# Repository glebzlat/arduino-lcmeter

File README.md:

## Arduino LC-meter

Простой измеритель емкости/индуктивности на Arduinо. Диапазон измерений: от ~90 пФ/мкГн до ~6 мкФ/Гн.

### Функционал

Кнопка J2 Calibration служит для программной коррекции нуля, что компенсирует начальное смещение нуля ОУ, а также емкость и индуктивность клемм и переключателя SW1. Нужный диапазон выбирается автоматически, причем после включения питания измерение начинается с 9 диапазона.

В процессе переключения диапазонов частота возбуждающего напряжения и результат преобразования АЦП отображаются в нижней строке индикатора. Это справочная информация, которая может помочь оценить корректность измерения параметров. Через несколько секунд после стабилизации показаний эта строка индикатора очищается, чтобы не отвлекать внимание пользователя.

Результат измерения отображается в верхней строке. Измеренное значение напряжения с выхода ОУ интерпретируется как емкость или индуктивность в зависимости от положения переключателя J3 MODE.

### Настройка

Прибор имеет два подстроечных резистора, предназначенных для настройки правильности показаний значения емкости и индуктивности. Их надо настроить после сборки и в дальнейшем трогать их не нужно. Для этой процедуры требуется парочка конденсаторов и индуктивностей с точностью хотя бы 5%.

### Как это работает

Принцип измерения заключается в подаче меандра на измеряемый конденсатор или индуктивность и преобразовании тока разряда конденсатора (или тока индуктивности) в напряжение, которое сглаживается и подается на АЦП Arduino. При измерении емкости конденсатор во время положительного полупериода заряжается через резистор R6 и диод D5, во время отрицательного разряжается через резистор R6 и диод D1, и его разрядный ток поступает на вход 2 U1. При измерении индуктивности во время положительного полупериода ток в катушке нарастает до значения, определяемого номиналом резистора R7, а во время отрицательной - ток, создаваемый ЭДС самоиндукции через D2 и R2, RV2 также поступает на вход U1. Ток разряда конденсатора (а, значит, и напряжение на выходе измерителя) прямо пропорционален его емкости, если конденсатор успевает полностью зарядиться за положительный полупериод и полностью разрядиться за отрицательный. Также и ток самоиндукции катушки прямо пропорционален ее индуктивности, если ток в ней успевает нарастать до максимального значения и спадать до нуля.

Для этого частота автоматически изменяется от 1 мегагерца до 15 герц в зависимости от значения напряжения на выходе измерителя. Прибор имеет 9 диапазонов измерения, и на каждом последующем диапазоне частота снижается, а предел измерения увеличивается в 4 раза. На первом диапазоне частота равна 1 МГц, и максимальное измеряемое значение ~90 пФ/мкГн.

| Диапазон | Частота (МГц) | Макс. емкость (Ф) | Макс. индуктивность (Гн) |
|----------|---------------|-------------------|--------------------------|
| 1        | 1.000.000     | 8,92e-11          | 8,92e-5                  |
| 2        | 250.000       | 3,56e-10          | 3,56e-4                  |
| 3        | 62.500        | 1,42e-9           | 1,42e-3                  |
| 4        | 15.625        | 5,70e-9           | 5,70e-3                  |
| 5        | 3.906         | 2,28e-8           | 2,28e-2                  |
| 6        | 976           | 9,13e-8           | 9,13e-2                  |
| 7        | 244           | 3,65e-7           | 3,65e-1                  |
| 8        | 61            | 1,46e-6           | 1,46                     |
| 9        | 15            | 5,84e-6           | 5,84                     |

### Источники

https://ra4nal.ontvtime.ru/lc_arduino.shtml

Журнал Радио №3 1982

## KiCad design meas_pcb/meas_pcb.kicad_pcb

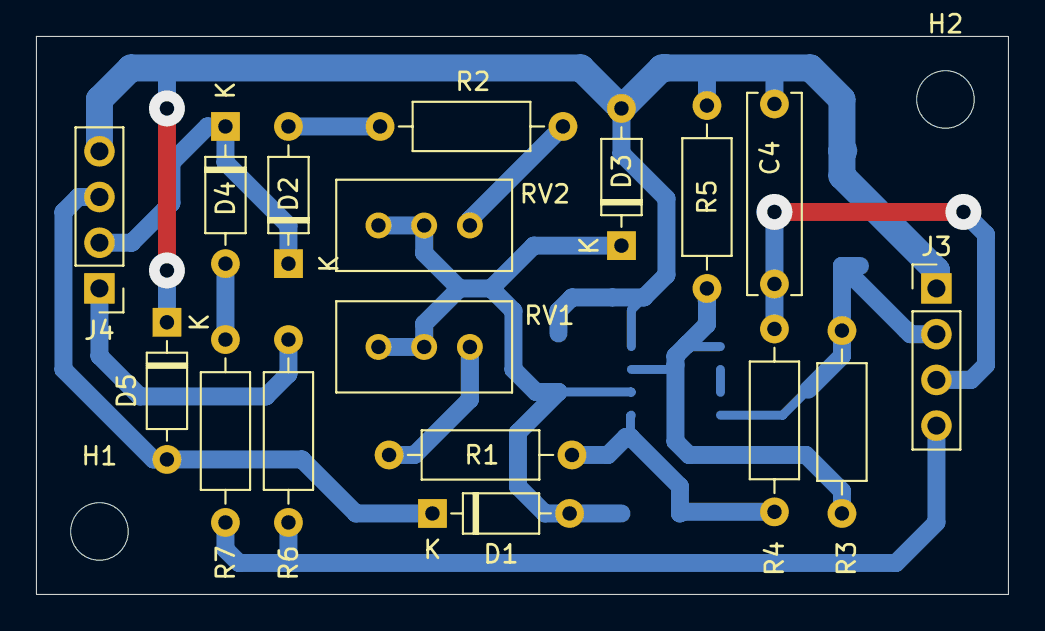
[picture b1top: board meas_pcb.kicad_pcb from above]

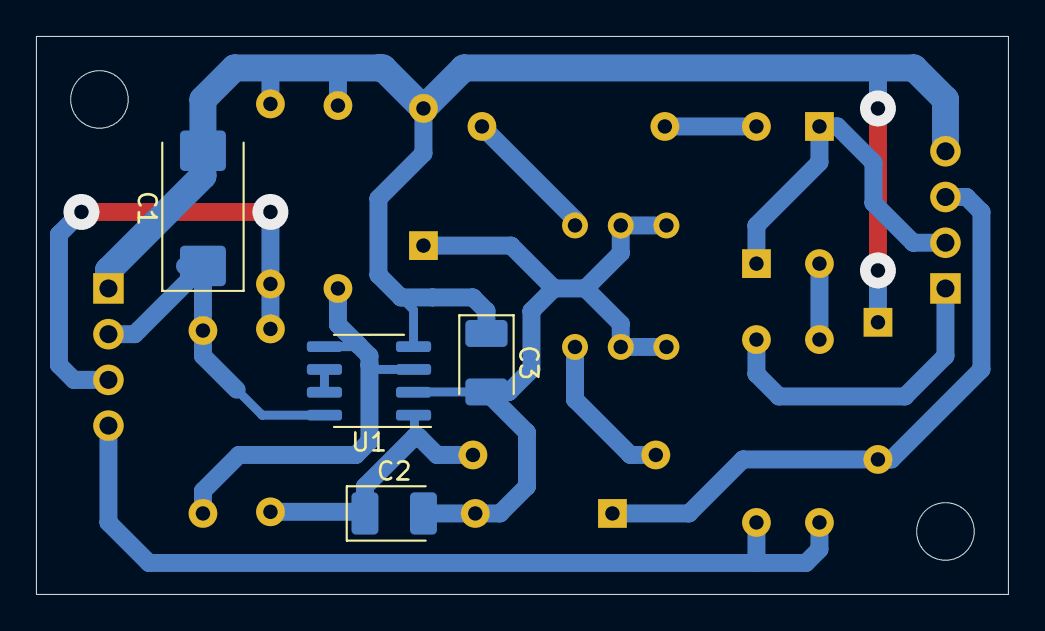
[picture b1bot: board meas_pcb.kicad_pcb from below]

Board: 2 copper layers, 54.0 x 31.0 mm, 23 parts (4 on the bottom side), 15 nets.

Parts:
C1: 22u; CP_EIA-7343-31_Kemet-D_Pad2.25x2.55mm_HandSolder
C2, C3: 47u; CP_EIA-3528-21_Kemet-B_Pad1.50x2.35mm_HandSolder
C4: 1000p; C_Rect_L11.0mm_W2.8mm_P10.00mm_MKT
D1, D2, D4, D5: BAT41; D_DO-35_SOD27_P7.62mm_Horizontal
D3: 1N4148; D_DO-35_SOD27_P7.62mm_Horizontal
H1, H2: MountingHole; MountingHole_3.2mm_M3
J3, J4: Conn_01x04; PinHeader_1x04_P2.54mm_Vertical
R1: 4.7k; R_Axial_DIN0207_L6.3mm_D2.5mm_P10.16mm_Horizontal
R2: 560; R_Axial_DIN0207_L6.3mm_D2.5mm_P10.16mm_Horizontal
R3: 47k; R_Axial_DIN0207_L6.3mm_D2.5mm_P10.16mm_Horizontal
R4: 3.3k; R_Axial_DIN0207_L6.3mm_D2.5mm_P10.16mm_Horizontal
R5, R7: 1k; R_Axial_DIN0207_L6.3mm_D2.5mm_P10.16mm_Horizontal
R6: 300; R_Axial_DIN0207_L6.3mm_D2.5mm_P10.16mm_Horizontal
RV1: 10k; Potentiometer_Bourns_3296W_Vertical
RV2: 1k; Potentiometer_Bourns_3296W_Vertical
U1: MCP6002-xMS; SOIC-8_3.9x4.9mm_P1.27mm

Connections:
/Vcc: C1.1, J3.2, R3.1, U1.8
GND: C1.2, C3.1, C4.2, D3.2, D5.1, J3.1, J4.4, R5.2, U1.4
unnamed: C2.1, R1.1, R4.2, U1.1
unnamed: C2.2, C3.2, D1.2, D3.1, RV1.1, RV1.2, RV2.1, RV2.2, U1.2
unnamed: C4.1, J3.3, R4.1
unnamed: D1.1, D5.2, J4.3
unnamed: D2.1, D4.1, J4.2
unnamed: D2.2, R2.2
unnamed: D4.2, R7.1
unnamed: J3.4, R6.2, R7.2
unnamed: J4.1, R6.1
unnamed: R1.2, RV1.3
unnamed: R2.1, RV2.3
unnamed: R3.2, R5.1, U1.3, U1.5
unnamed: U1.6, U1.7

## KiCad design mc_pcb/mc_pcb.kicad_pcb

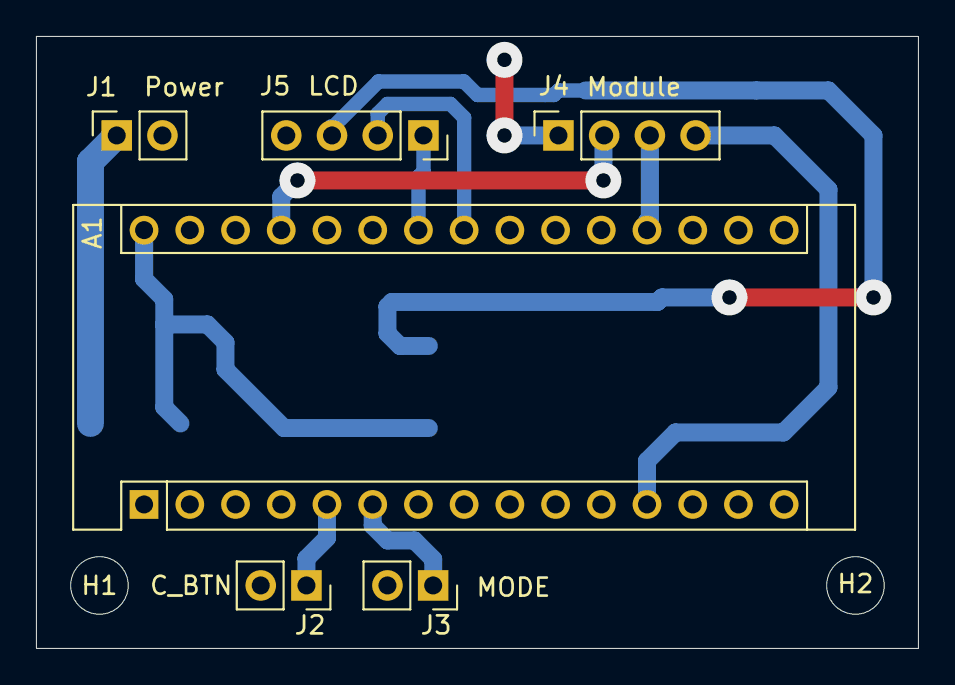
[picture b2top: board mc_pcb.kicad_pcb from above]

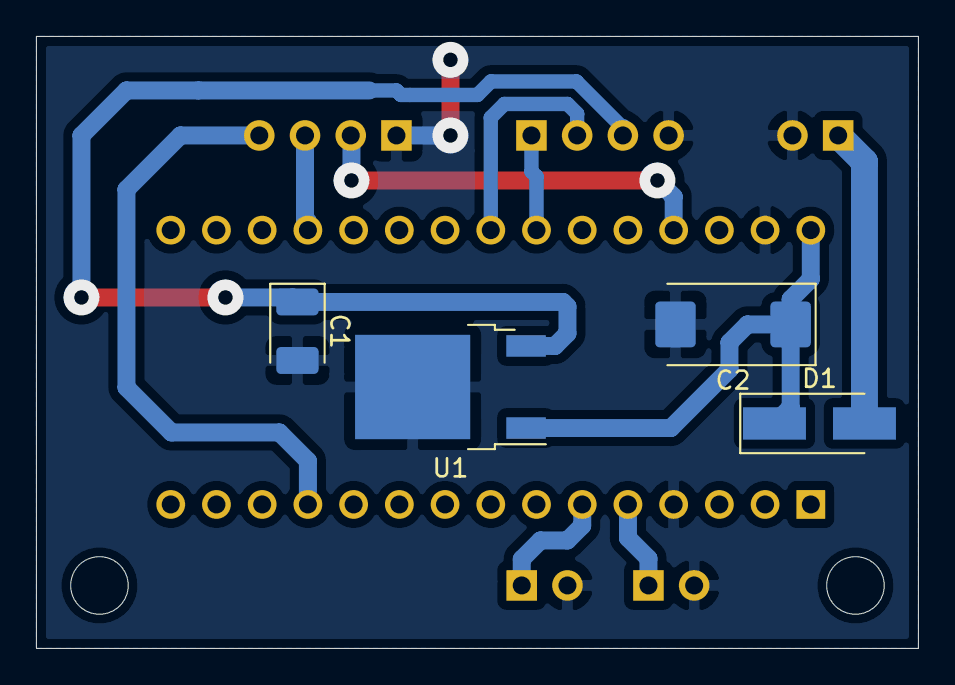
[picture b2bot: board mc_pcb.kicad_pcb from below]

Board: 2 copper layers, 49.0 x 34.0 mm, 12 parts (4 on the bottom side), 11 nets.

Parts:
A1: Arduino_Nano_v3.x; Arduino_Nano
C1: 47u; CP_EIA-3528-21_Kemet-B_Pad1.50x2.35mm_HandSolder
C2: 22u; CP_EIA-7343-31_Kemet-D_Pad2.25x2.55mm_HandSolder
D1: 1N4004; D_SMA_Handsoldering
H1, H2: MountingHole; MountingHole_3.2mm_M3
J1: Power; PinSocket_1x02_P2.54mm_Vertical
J2: C_BTN; PinSocket_1x02_P2.54mm_Vertical
J3: MODE; PinSocket_1x02_P2.54mm_Vertical
J4: Module; PinSocket_1x04_P2.54mm_Vertical
J5: LCD; PinSocket_1x04_P2.54mm_Vertical
U1: LM78M05_TO252; TO-252-2

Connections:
/FRQ: A1.12, J4.4
/VCC: A1.27, J4.2
/VDD: C1.1, J5.3, U1.3
GND: A1.4, A1.29, C1.2, C2.2, J1.2, J2.2, J3.2, J4.1, J5.4, U1.2
unnamed: A1.5, J2.1
unnamed: A1.6, J3.1
unnamed: A1.19, J4.3
unnamed: A1.23, J5.2
unnamed: A1.24, J5.1
unnamed: A1.30, C2.1, D1.1, U1.1
unnamed: D1.2, J1.1

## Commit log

2022-11-06 repair readme
2022-11-06 some changes in readme
2022-11-06 additional info in readme
